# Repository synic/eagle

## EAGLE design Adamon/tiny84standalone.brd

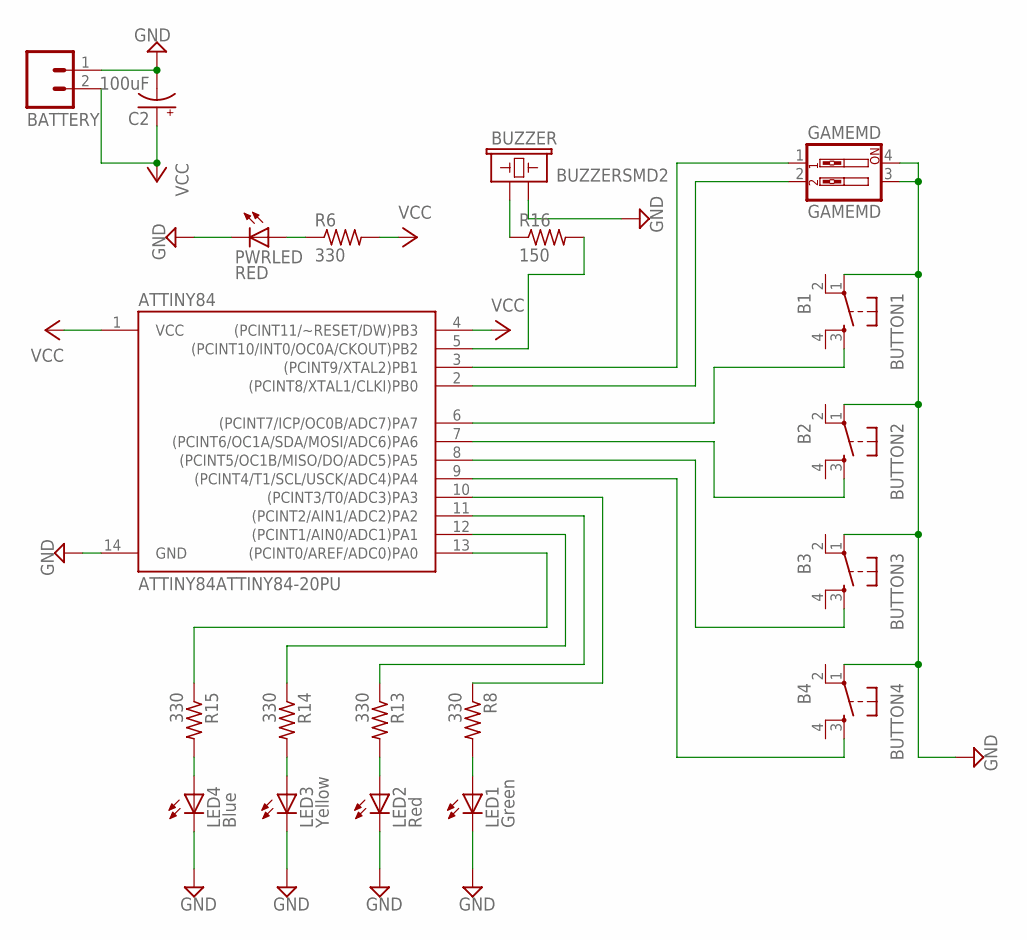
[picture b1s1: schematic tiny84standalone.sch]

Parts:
ATTINY84: ATTINY84ATTINY84-20PU; DIL14
BATTERY: M02JST-PTH-VERT; JST-2-PTH-VERT
BUTTON1: B1; TACTILE-PTH
BUTTON2: B2; TACTILE-PTH
BUTTON3: B3; TACTILE-PTH
BUTTON4: B4; TACTILE-PTH
BUZZER: BUZZERSMD2; BUZZER-CCV
C2: 100uF; CPOL-RADIAL-100UF-25V
GAMEMD: GAMEMD; DIPSWITCH-02
LED1: Green; LED5MM
LED2: Red; LED5MM
LED3: Yellow; LED5MM
LED4: Blue; LED5MM
PWRLED: RED; CHIPLED_0805
R6, R8, R13, R14, R15: 330; R0805
R16: 150; R0805

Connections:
GND: ATTINY84.14 (GND), BATTERY.1, BUTTON1.1, BUTTON2.1, BUTTON3.1, BUTTON4.1, BUZZER.- (2), C2.2 (-), GAMEMD.3, GAMEMD.4, LED1.K (C), LED2.K (C), LED3.K (C), LED4.K (C), PWRLED.C
unnamed: BUZZER.+ (1), R16.1
unnamed: PWRLED.A, R6.1
unnamed: LED1.A, R8.2
unnamed: LED2.A, R13.2
unnamed: ATTINY84.6 ((PCINT7/ICP/OC0B/ADC7)PA7), BUTTON1.3
unnamed: ATTINY84.5 ((PCINT10/INT0/OC0A/CKOUT)PB2), R16.2
unnamed: LED3.A, R14.2
unnamed: LED4.A, R15.2
unnamed: ATTINY84.7 ((PCINT6/OC1A/SDA/MOSI/ADC6)PA6), BUTTON2.3
unnamed: ATTINY84.3 ((PCINT9/XTAL2)PB1), GAMEMD.1
unnamed: ATTINY84.2 ((PCINT8/XTAL1/CLKI)PB0), GAMEMD.2
unnamed: ATTINY84.8 ((PCINT5/OC1B/MISO/DO/ADC5)PA5), BUTTON3.3
unnamed: ATTINY84.9 ((PCINT4/T1/SCL/USCK/ADC4)PA4), BUTTON4.3
unnamed: ATTINY84.10 ((PCINT3/T0/ADC3)PA3), R8.1
unnamed: ATTINY84.11 ((PCINT2/AIN1/ADC2)PA2), R13.1
unnamed: ATTINY84.12 ((PCINT1/AIN0/ADC1)PA1), R14.1
unnamed: ATTINY84.13 ((PCINT0/AREF/ADC0)PA0), R15.1
VCC: ATTINY84.1 (VCC), ATTINY84.4 ((PCINT11/~RESET/DW)PB3), BATTERY.2, C2.1 (+), R6.2

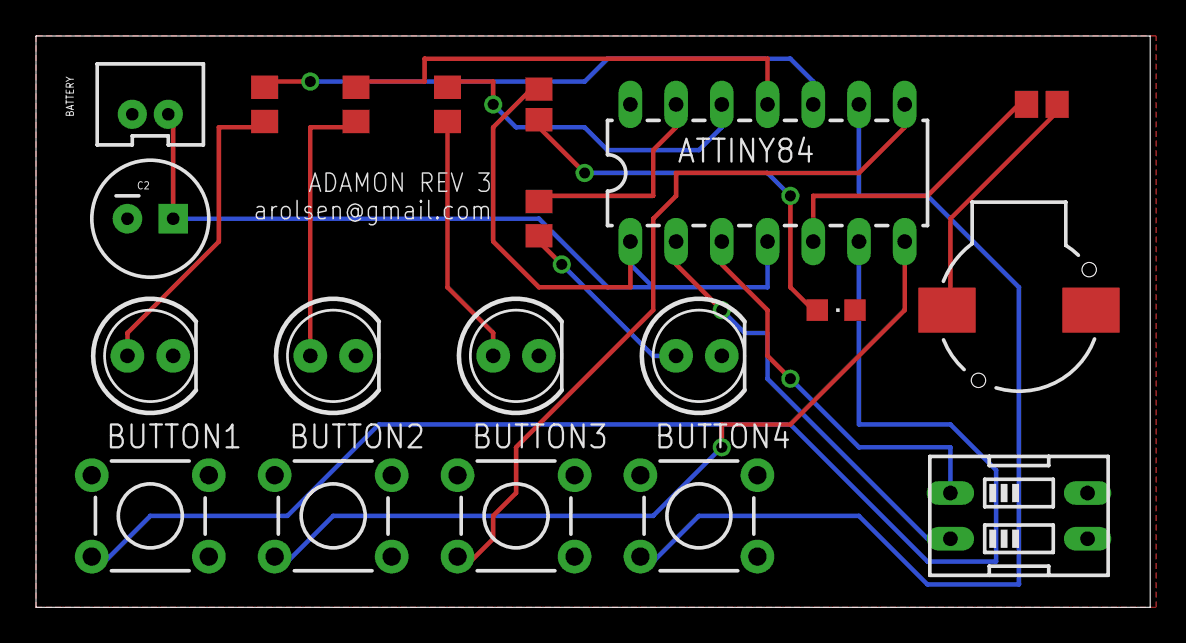
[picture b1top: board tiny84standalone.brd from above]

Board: 2 copper layers, 61.9 x 31.7 mm, 20 parts (0 on the bottom side), 19 nets.

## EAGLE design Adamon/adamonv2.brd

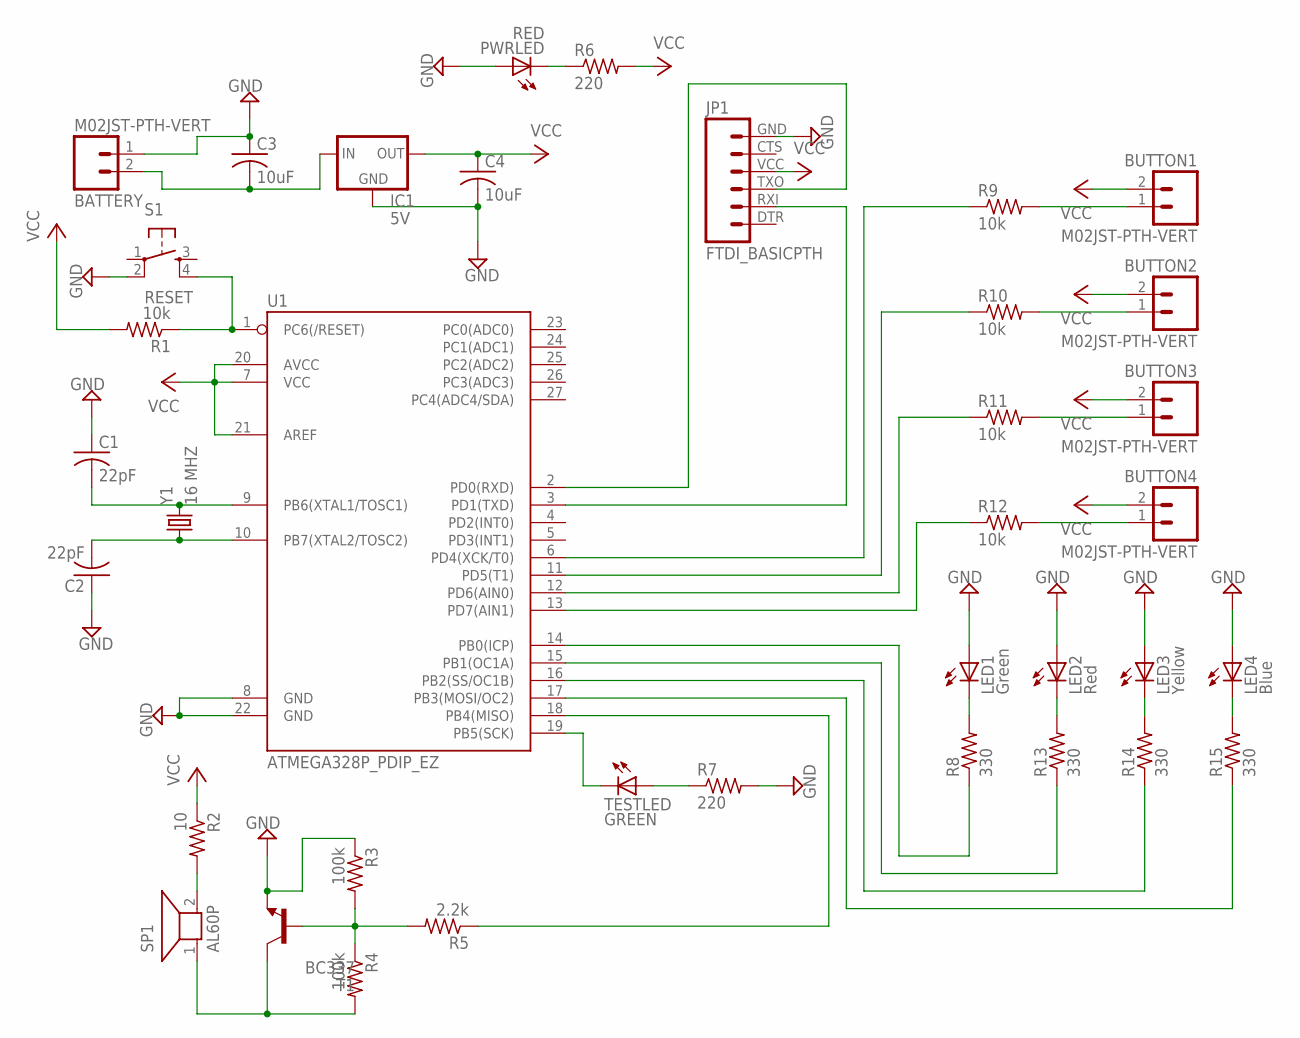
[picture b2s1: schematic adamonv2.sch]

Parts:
BATTERY: M02JST-PTH-VERT; JST-2-PTH-VERT
BUTTON1, BUTTON2, BUTTON3, BUTTON4: M02JST-PTH-VERT; JST-2-PTH-VERT
C1, C2: 22pF; C0805
C3, C4: 10uF; C0805
IC1: 5V; TO220-IGO
JP1: FTDI_BASICPTH; FTDI_BASIC
LED1: Green; LED5MM
LED2: Red; LED5MM
LED3: Yellow; LED5MM
LED4: Blue; LED5MM
PWRLED: RED; CHIPLED_0805
R1, R9, R10, R11, R12: 10k; R0805
R2: 10; R0805
R3, R4: 100k; R0805
R5: 2.2k; R0805
R6, R7: 220; R0805
R8, R13, R14, R15: 330; R0805
S1: RESET; TACTILE_SWITCH_SMD
SP1: AL60P
T1: BC337; TO92
TESTLED: GREEN; CHIPLED_0805
U1: ATMEGA328P_PDIP_EZ; DIL28-EZ
Y1: 16 MHZ; HC49US

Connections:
GND: BATTERY.1, C1.1, C2.1, C3.1, C4.2, IC1.GND, JP1.GND (6), LED1.A, LED2.A, LED3.A, LED4.A, PWRLED.A, R3.1, R7.2, S1.2, T1.1 (E), U1.8 (GND), U1.22 (GND)
unnamed: C1.2, U1.9 (PB6(XTAL1/TOSC1)), Y1.2
unnamed: BATTERY.2, C3.2, IC1.IN
unnamed: PWRLED.C, R6.1
unnamed: R1.1, S1.4, U1.1 (PC6(/RESET))
unnamed: C2.2, U1.10 (PB7(XTAL2/TOSC2)), Y1.1
unnamed: TESTLED.C, U1.19 (PB5(SCK))
unnamed: R7.1, TESTLED.A
unnamed: JP1.TXO (3), U1.2 (PD0(RXD))
unnamed: JP1.RXI (2), U1.3 (PD1(TXD))
unnamed: R15.1, U1.17 (PB3(MOSI/OC2))
unnamed: R14.1, U1.16 (PB2(SS/OC1B))
unnamed: R12.1, U1.13 (PD7(AIN1))
unnamed: BUTTON1.1, R9.2
unnamed: R11.1, U1.12 (PD6(AIN0))
unnamed: BUTTON2.1, R10.2
unnamed: R10.1, U1.11 (PD5(T1))
unnamed: BUTTON3.1, R11.2
unnamed: R9.1, U1.6 (PD4(XCK/T0))
unnamed: BUTTON4.1, R12.2
unnamed: R3.2, R4.1, R5.2, T1.2 (B)
unnamed: R4.2, SP1.1, T1.3 (C)
unnamed: R2.2, SP1.2
unnamed: R5.1, U1.18 (PB4(MISO))
unnamed: LED4.K (C), R15.2
unnamed: LED3.K (C), R14.2
unnamed: R13.1, U1.15 (PB1(OC1A))
unnamed: LED2.K (C), R13.2
unnamed: R8.1, U1.14 (PB0(ICP))
unnamed: LED1.K (C), R8.2
VCC: BUTTON1.2, BUTTON2.2, BUTTON3.2, BUTTON4.2, C4.1, IC1.OUT, JP1.VCC (4), R1.2, R2.1, R6.2, U1.7 (VCC), U1.20 (AVCC), U1.21 (AREF)

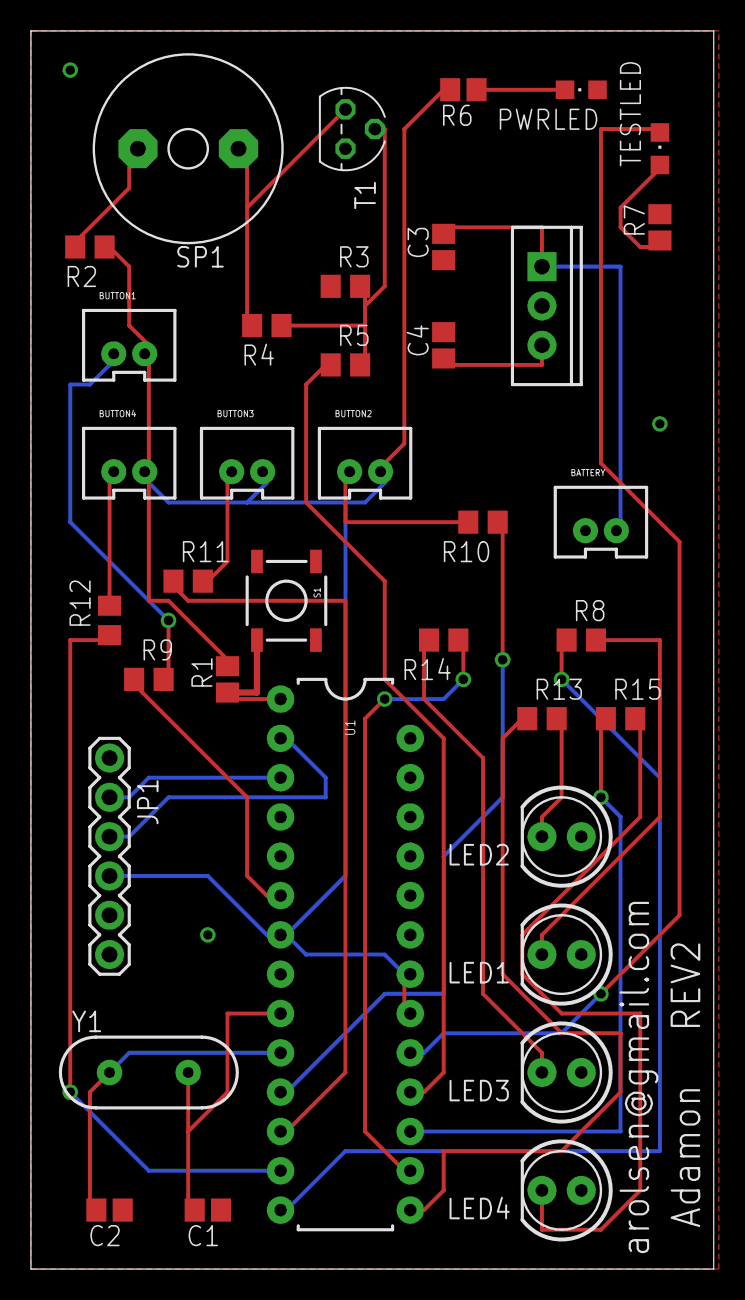
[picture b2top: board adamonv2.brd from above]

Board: 2 copper layers, 44.1 x 80.0 mm, 37 parts (0 on the bottom side), 31 nets.

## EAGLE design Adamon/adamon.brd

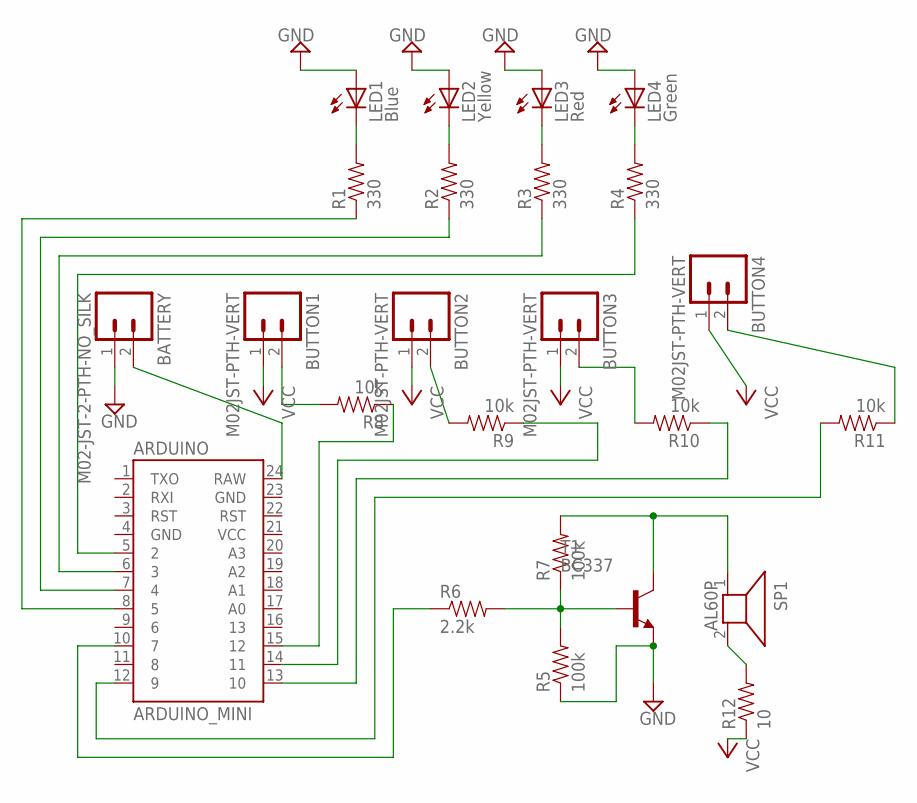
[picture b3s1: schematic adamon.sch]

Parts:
ARDUINO: ARDUINO_MINI
BATTERY: M02-JST-2-PTH-NO_SILK; JST-2-PTH-NS
BUTTON1, BUTTON2, BUTTON3, BUTTON4: M02JST-PTH-VERT; JST-2-PTH-VERT
LED1: Blue; LED5MM
LED2: Yellow; LED5MM
LED3: Red; LED5MM
LED4: Green; LED5MM
R1, R2, R3, R4: 330; AXIAL-0.4
R5, R7: 100k; AXIAL-0.4
R6: 2.2k; AXIAL-0.4
R8, R9, R10, R11: 10k; AXIAL-0.4
R12: 10; AXIAL-0.4
SP1: AL60P
T1: BC337; TO92

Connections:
GND: BATTERY.1, LED1.A, LED2.A, LED3.A, LED4.A, R5.P$1 (1), T1.1 (E)
unnamed: LED1.K (C), R1.P$2 (2)
unnamed: ARDUINO.8 (5), R1.P$1 (1)
unnamed: ARDUINO.7 (4), R2.P$1 (1)
unnamed: ARDUINO.6 (3), R3.P$1 (1)
unnamed: ARDUINO.5 (2), R4.P$1 (1)
unnamed: LED2.K (C), R2.P$2 (2)
unnamed: LED3.K (C), R3.P$2 (2)
unnamed: LED4.K (C), R4.P$2 (2)
unnamed: BUTTON4.2, R11.P$1 (1)
unnamed: BUTTON3.2, R10.P$2 (2)
unnamed: BUTTON2.2, R9.P$2 (2)
unnamed: ARDUINO.24 (RAW), BATTERY.2
unnamed: ARDUINO.15 (12), R8.P$1 (1)
unnamed: ARDUINO.14 (11), R9.P$1 (1)
unnamed: ARDUINO.13 (10), R10.P$1 (1)
unnamed: ARDUINO.12 (9), R11.P$2 (2)
unnamed: R5.P$2 (2), R6.P$2 (2), R7.P$1 (1), T1.2 (B)
unnamed: R7.P$2 (2), SP1.1, T1.3 (C)
unnamed: R12.P$2 (2), SP1.2
unnamed: BUTTON1.2, R8.P$2 (2)
SPKAMP: ARDUINO.10 (7), R6.P$1 (1)
VCC: BUTTON1.1, BUTTON2.1, BUTTON3.1, BUTTON4.1, R12.P$1 (1)

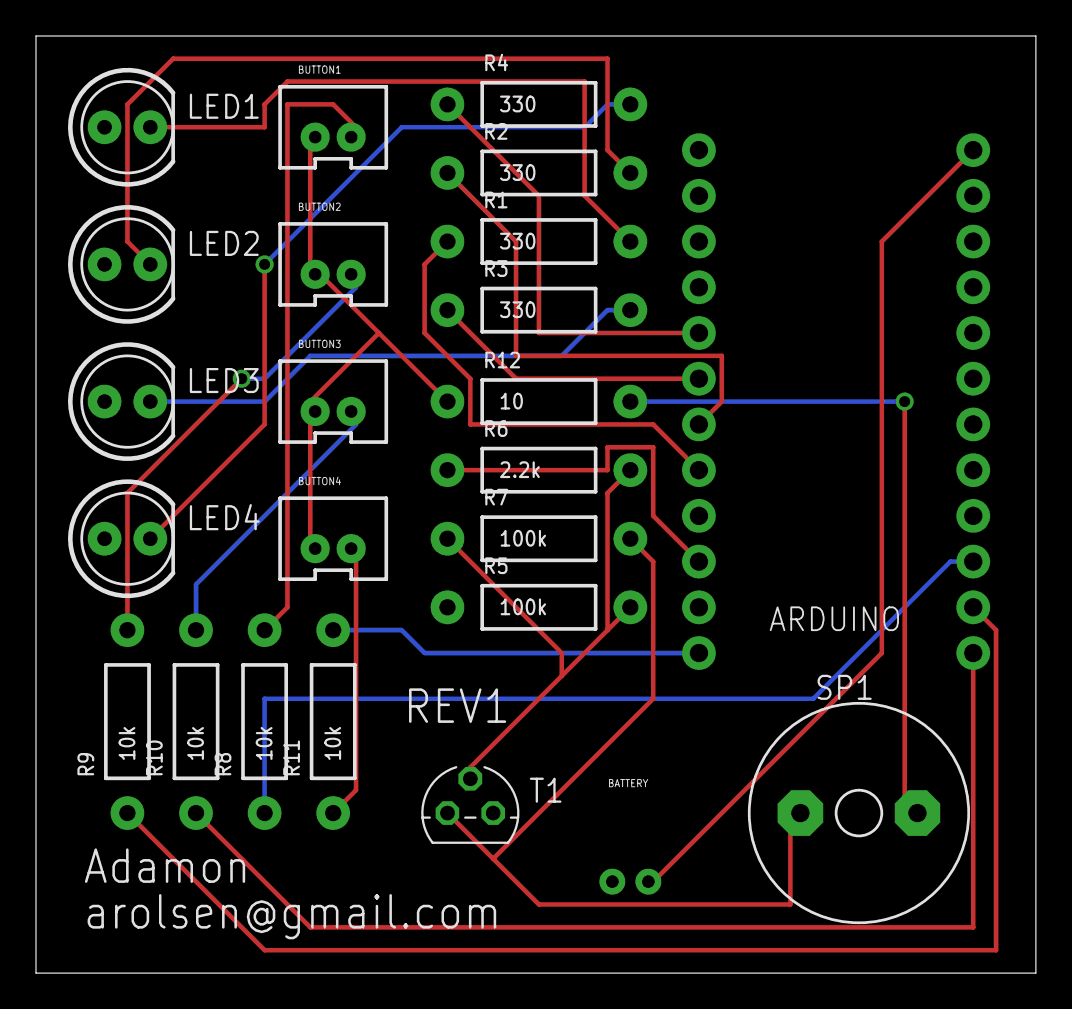
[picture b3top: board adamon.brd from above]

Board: 2 copper layers, 55.5 x 52.1 mm, 24 parts (0 on the bottom side), 23 nets.

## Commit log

2013-12-31 started repo
2013-12-31 updated schematic
2014-01-02 add stuff
2014-01-06 add tiny84standalone
2014-01-06 update tiny84
2014-01-07 awh yeah
2014-01-07 better schematic
2014-01-07 woot
2014-03-18 almost done with tssop stm32 package

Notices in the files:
parts and their libraries:
SparkFun-Boards: Licensing: CC v3.0 Share-Alike You are welcome to use this library for commercial purposes.
